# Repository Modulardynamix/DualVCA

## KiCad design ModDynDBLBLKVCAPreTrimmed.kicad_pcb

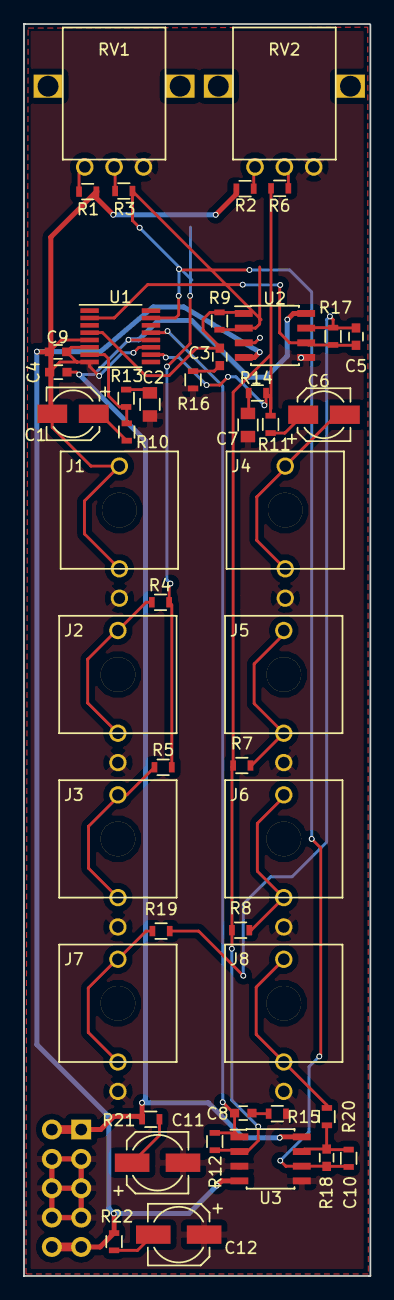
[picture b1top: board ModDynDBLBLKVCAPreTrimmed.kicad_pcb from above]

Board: 2 copper layers, 30.0 x 108.3 mm, 48 parts (1 on the bottom side), 33 nets.

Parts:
C1: 10u; c_elec_4x5.8
C2, C7: 100pf; C_0805
C3, C8: 1500pf; C_0603
C4, C9: C_Small; C_0603
C5, C10: 22pf; C_0603
C6: 10uf; c_elec_4x5.8
C11, C12: 22uf; c_elec_5x5.8
J1: AUDIO_INPUT_A; Thonkicon_3.5mm_Switching_Jack_Socket
J2: CV_INPUT_A1; Thonkicon_3.5mm_Switching_Jack_Socket
J3: CV_INPUT_A2; Thonkicon_3.5mm_Switching_Jack_Socket
J4: AUDIO_INPUT_B; Thonkicon_3.5mm_Switching_Jack_Socket
J5: CV_INPUT_B1; Thonkicon_3.5mm_Switching_Jack_Socket
J6: CV_INPUT_B2; Thonkicon_3.5mm_Switching_Jack_Socket
J7: AUDIO_OUTPUT_A; Thonkicon_3.5mm_Switching_Jack_Socket
J8: AUDIO_OUTPUT_B; Thonkicon_3.5mm_Switching_Jack_Socket
P1: CONN_02X05; Pin_Header_Straight_2x05
R1, R2, R6, R7, R8, R12, R15: R; R_0603
R3, R4, R5: 47K; R_0603
R9, R13, R14: 6K8; R_0603
R10, R11, R17, R18: 20K; R_0603
R16: 100R; R_0603
R19, R20: 470R; R_0603
R21, R22: 10R; R_0603
RV1, RV2: POT; Verticle_Pot_New
U1: THAT2162; QSOP-16_3.9x4.9mm_Pitch0.635mm
U2, U3: NJM4580; SOIC-8_3.9x4.9mm_Pitch1.27mm

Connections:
GND: C2.2, C4.1, C7.1, C9.1, C11.2, C12.1, J1.1, J2.1, J3.1, J4.1, J5.1, J6.1, J7.1, J8.1, P1.3, P1.4, P1.5, P1.6, P1.7, P1.8, R15.1, R16.2, RV1.3, RV2.3, U1.6, U1.8, U1.11, U2.3, U2.5, U3.3, U3.5
unnamed: C1.1, R10.2
unnamed: C1.2, J1.2, J1.3
unnamed: C2.1, R13.2
unnamed: C3.1, R16.1
unnamed: C3.2, R9.1, U1.4, U2.1
unnamed: C5.1, R17.1, R19.2, U2.7
unnamed: C5.2, R17.2, U1.2, U2.6
unnamed: C6.1, R11.2
unnamed: C6.2, J4.2, J4.3
unnamed: C7.2, R14.1
unnamed: C8.1, R15.2
unnamed: C8.2, R12.1, U1.13, U3.1
unnamed: C10.1, R18.1, R20.2, U3.7
unnamed: C10.2, R18.2, U1.15, U3.6
unnamed: C11.1, R21.2
unnamed: C12.2, R22.1
unnamed: J2.2, J2.3, R4.2
unnamed: J3.2, J3.3, R5.2
unnamed: J5.2, J5.3, R7.2
unnamed: J6.2, J6.3, R8.2
unnamed: J7.2, J7.3, R19.1
unnamed: J8.2, J8.3, R20.1
unnamed: R1.2, RV1.1
unnamed: R2.1, RV2.1
unnamed: R3.1, R4.1, R5.1, R9.2, U2.2
unnamed: R3.2, RV1.2
unnamed: R6.2, RV2.2
unnamed: R10.1, R13.1, U1.7
unnamed: R11.1, R14.2, U1.10
unnamed: R6.1, R7.1, R8.1, R12.2, U3.2
VCC: C4.2, P1.1, P1.2, R21.1, U1.12, U2.8, U3.8
VEE: C9.2, P1.9, P1.10, R1.1, R2.2, R22.2, U1.5, U2.4, U3.4

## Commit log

2018-03-27 Revision 1.1
    Committer: ModularDynamix <modulardynamix@gmail.com>
    On branch master
    Initial commit
    Changes to be committed:
    new file: ModDynDBLBLKVCAPreTrimmed.kicad_pcb
    new file: ModDynDBLBLKVCAPreTrimmed.pro
